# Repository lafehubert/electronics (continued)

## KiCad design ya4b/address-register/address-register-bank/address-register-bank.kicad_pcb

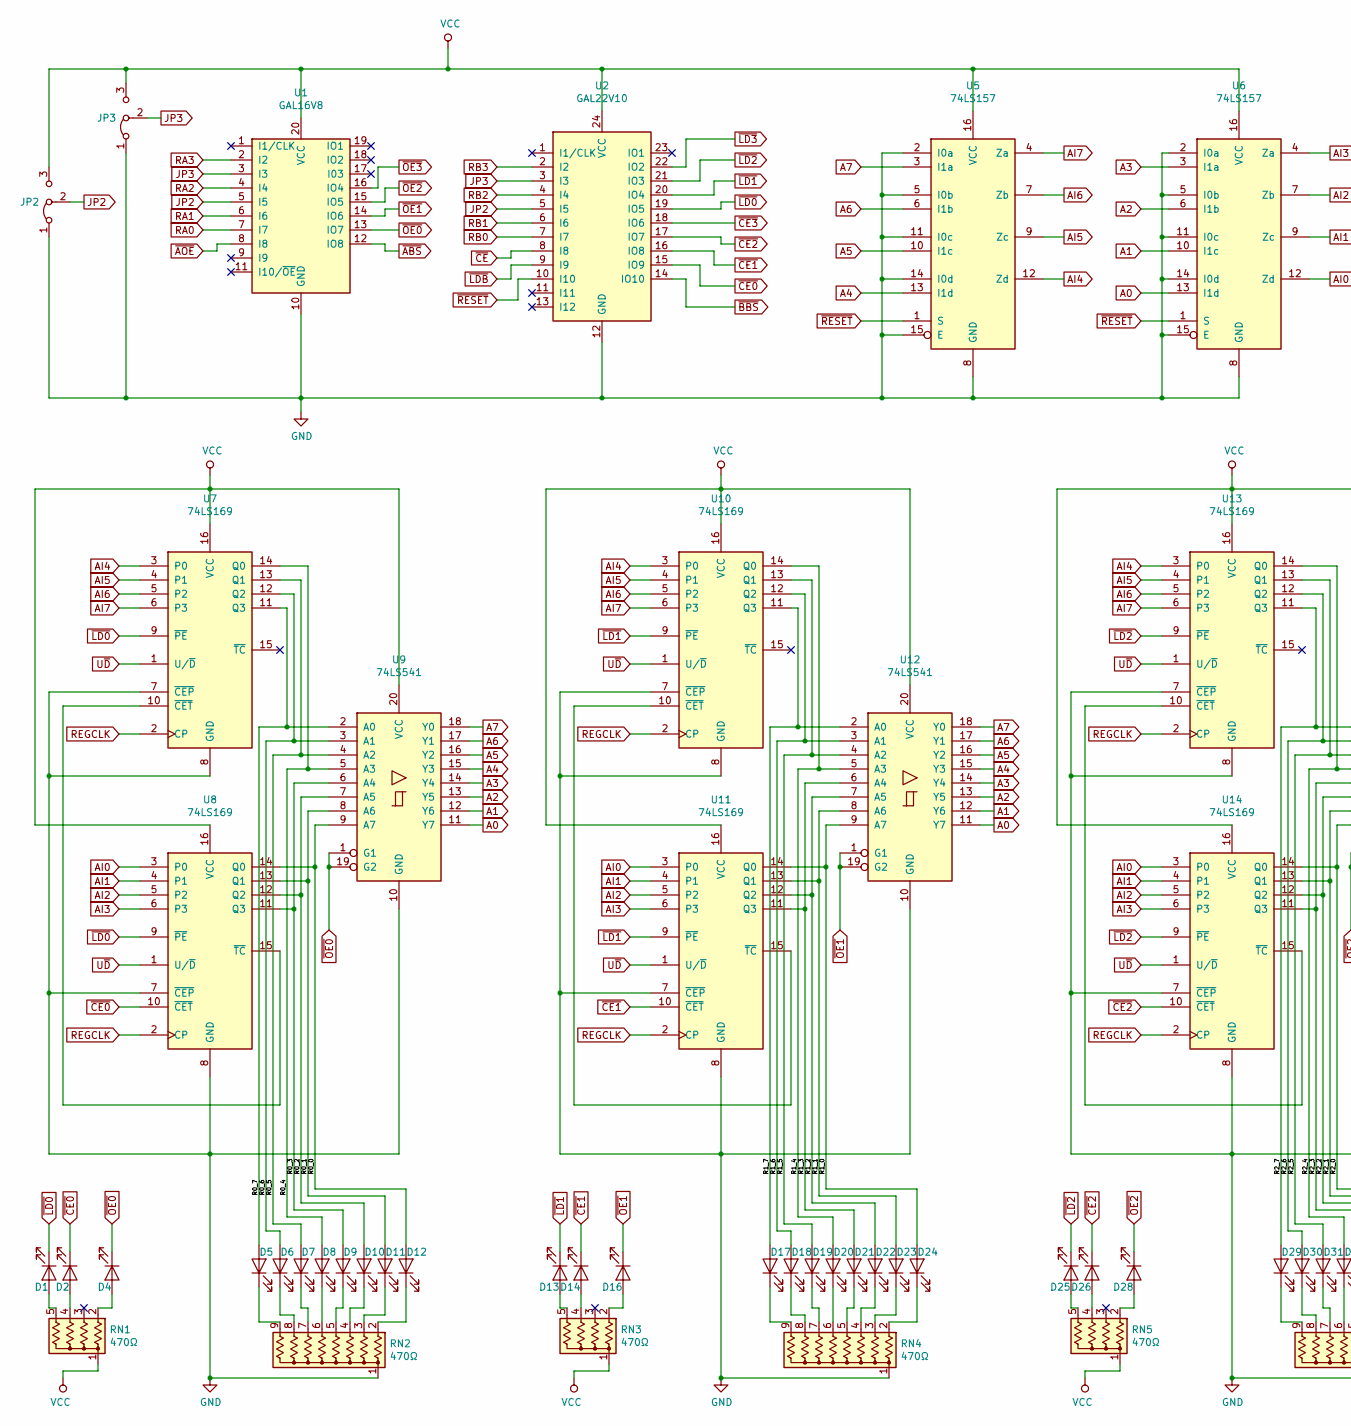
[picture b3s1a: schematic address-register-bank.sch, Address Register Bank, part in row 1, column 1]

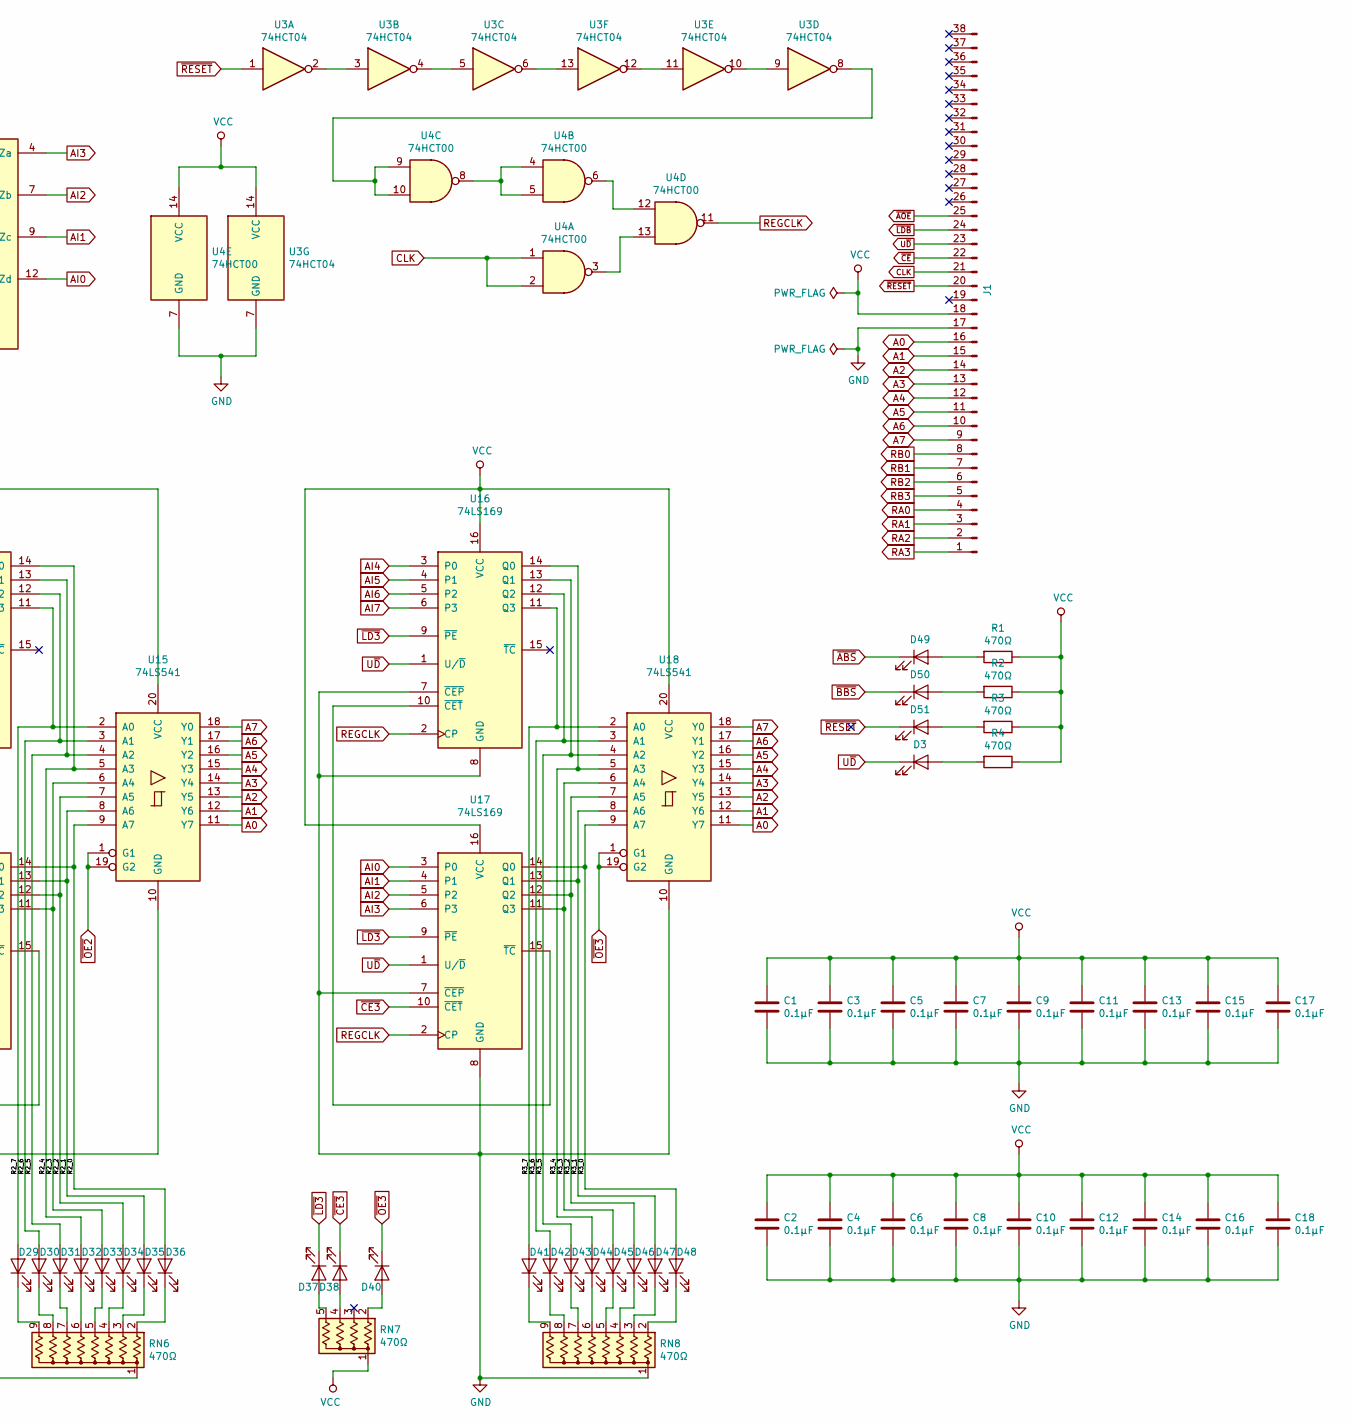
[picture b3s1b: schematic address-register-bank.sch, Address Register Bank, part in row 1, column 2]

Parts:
C1, C2, C3, C4, C5, C6, C7, C8, C9, C10, C11, C12, C13, C14, C15, C16, C17, C18: 0.1µF; C_Disc_D3.0mm_W1.6mm_P2.50mm
D1, D2, D3, D4, D5, D6, D7, D8, D9, D10, D11, D12, D13, D14, D16, D17, D18, D19, D20, D21, D22, D23, D24, D25, D26, D28, D29, D30, D31, D32, D33, D34, D35, D36, D37, D38, D40, D41, D42, D43, D44, D45, D46, D47, D48, D49, D50, D51: LED; LED_Rectangular_W5.0mm_H2.0mm
J1: Conn_01x38_Male; PinHeader_1x38_P2.54mm_Vertical
JP2, JP3: Jumper_3_Bridged12; PinHeader_1x03_P2.54mm_Vertical
R1, R2, R3, R4: 470Ω; R_Axial_DIN0207_L6.3mm_D2.5mm_P10.16mm_Horizontal
RN1, RN3, RN5, RN7: 470Ω; R_Array_SIP5
RN2, RN4, RN6, RN8: 470Ω; R_Array_SIP9
U1: GAL16V8; DIP-20_W7.62mm_Socket
U2: GAL22V10; DIP-24_W7.62mm_Socket
U3: 74HCT04; DIP-14_W7.62mm_Socket
U4: 74HCT00; DIP-14_W7.62mm_Socket
U5, U6: 74LS157; DIP-16_W7.62mm_Socket
U7, U8, U10, U11, U13, U14, U16, U17: 74LS169; DIP-16_W7.62mm_Socket
U9, U12, U15, U18: 74LS541; DIP-20_W7.62mm_Socket

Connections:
/R0_0: D12.2 (A), U8.14 (Q0), U9.9 (A7)
/R0_1: D11.2 (A), U8.13 (Q1), U9.8 (A6)
/R0_2: D10.2 (A), U8.12 (Q2), U9.7 (A5)
/R0_3: D9.2 (A), U8.11 (Q3), U9.6 (A4)
/R0_4: D8.2 (A), U7.14 (Q0), U9.5 (A3)
/R0_5: D7.2 (A), U7.13 (Q1), U9.4 (A2)
/R0_6: D6.2 (A), U7.12 (Q2), U9.3 (A1)
/R0_7: D5.2 (A), U7.11 (Q3), U9.2 (A0)
/R1_0: D24.2 (A), U11.14 (Q0), U12.9 (A7)
/R1_1: D23.2 (A), U11.13 (Q1), U12.8 (A6)
/R1_2: D22.2 (A), U11.12 (Q2), U12.7 (A5)
/R1_3: D21.2 (A), U11.11 (Q3), U12.6 (A4)
/R1_4: D20.2 (A), U10.14 (Q0), U12.5 (A3)
/R1_5: D19.2 (A), U10.13 (Q1), U12.4 (A2)
/R1_6: D18.2 (A), U10.12 (Q2), U12.3 (A1)
/R1_7: D17.2 (A), U10.11 (Q3), U12.2 (A0)
/R2_0: D36.2 (A), U14.14 (Q0), U15.9 (A7)
/R2_1: D35.2 (A), U14.13 (Q1), U15.8 (A6)
/R2_2: D34.2 (A), U14.12 (Q2), U15.7 (A5)
/R2_3: D33.2 (A), U14.11 (Q3), U15.6 (A4)
/R2_4: D32.2 (A), U13.14 (Q0), U15.5 (A3)
/R2_5: D31.2 (A), U13.13 (Q1), U15.4 (A2)
/R2_6: D30.2 (A), U13.12 (Q2), U15.3 (A1)
/R2_7: D29.2 (A), U13.11 (Q3), U15.2 (A0)
/R3_0: D48.2 (A), U17.14 (Q0), U18.9 (A7)
/R3_1: D47.2 (A), U17.13 (Q1), U18.8 (A6)
/R3_2: D46.2 (A), U17.12 (Q2), U18.7 (A5)
/R3_3: D45.2 (A), U17.11 (Q3), U18.6 (A4)
/R3_4: D44.2 (A), U16.14 (Q0), U18.5 (A3)
/R3_5: D43.2 (A), U16.13 (Q1), U18.4 (A2)
/R3_6: D42.2 (A), U16.12 (Q2), U18.3 (A1)
/R3_7: D41.2 (A), U16.11 (Q3), U18.2 (A0)
A0: J1.16, U6.13 (I1d), U9.11 (Y7), U12.11 (Y7), U15.11 (Y7), U18.11 (Y7)
A1: J1.15, U6.10 (I1c), U9.12 (Y6), U12.12 (Y6), U15.12 (Y6), U18.12 (Y6)
A2: J1.14, U6.6 (I1b), U9.13 (Y5), U12.13 (Y5), U15.13 (Y5), U18.13 (Y5)
A3: J1.13, U6.3 (I1a), U9.14 (Y4), U12.14 (Y4), U15.14 (Y4), U18.14 (Y4)
A4: J1.12, U5.13 (I1d), U9.15 (Y3), U12.15 (Y3), U15.15 (Y3), U18.15 (Y3)
A5: J1.11, U5.10 (I1c), U9.16 (Y2), U12.16 (Y2), U15.16 (Y2), U18.16 (Y2)
A6: J1.10, U5.6 (I1b), U9.17 (Y1), U12.17 (Y1), U15.17 (Y1), U18.17 (Y1)
A7: J1.9, U5.3 (I1a), U9.18 (Y0), U12.18 (Y0), U15.18 (Y0), U18.18 (Y0)
AI0: U6.12 (Zd), U8.3 (P0), U11.3 (P0), U14.3 (P0), U17.3 (P0)
AI1: U6.9 (Zc), U8.4 (P1), U11.4 (P1), U14.4 (P1), U17.4 (P1)
AI2: U6.7 (Zb), U8.5 (P2), U11.5 (P2), U14.5 (P2), U17.5 (P2)
AI3: U6.4 (Za), U8.6 (P3), U11.6 (P3), U14.6 (P3), U17.6 (P3)
AI4: U5.12 (Zd), U7.3 (P0), U10.3 (P0), U13.3 (P0), U16.3 (P0)
AI5: U5.9 (Zc), U7.4 (P1), U10.4 (P1), U13.4 (P1), U16.4 (P1)
AI6: U5.7 (Zb), U7.5 (P2), U10.5 (P2), U13.5 (P2), U16.5 (P2)
AI7: U5.4 (Za), U7.6 (P3), U10.6 (P3), U13.6 (P3), U16.6 (P3)
CLK: J1.21, U4.1, U4.2
GND: C1.2, C2.2, C3.2, C4.2, C5.2, C6.2, C7.2, C8.2, C9.2, C10.2, C11.2, C12.2, C13.2, C14.2, C15.2, C16.2, C17.2, C18.2, J1.17, JP2.1 (A), JP3.1 (A), RN2.1 (common), RN4.1 (common), RN6.1 (common), RN8.1 (common), U1.10 (GND), U2.12 (GND), U3.7 (GND), U4.7 (GND), U5.2 (I0a), U5.5 (I0b), U5.8 (GND), U5.11 (I0c), U5.14 (I0d), U5.15 (E), U6.2 (I0a), U6.5 (I0b), U6.8 (GND), U6.11 (I0c), U6.14 (I0d), U6.15 (E), U7.7 (~CEP), U7.8 (GND), U8.7 (~CEP), U8.8 (GND), U9.10 (GND), U10.7 (~CEP), U10.8 (GND), U11.7 (~CEP), U11.8 (GND), U12.10 (GND), U13.7 (~CEP), U13.8 (GND), U14.7 (~CEP), U14.8 (GND), U15.10 (GND), U16.7 (~CEP), U16.8 (GND), U17.7 (~CEP), U17.8 (GND), U18.10 (GND)
JP2: JP2.2 (C), U1.5 (I5), U2.5 (I5)
JP3: JP3.2 (C), U1.3 (I3), U2.3 (I3)
unnamed: D1.2 (A), RN1.5 (R4)
unnamed: D2.2 (A), RN1.4 (R3)
unnamed: D3.2 (A), R4.2
unnamed: D4.2 (A), RN1.2 (R1)
unnamed: D5.1 (K), RN2.9 (R8)
unnamed: D6.1 (K), RN2.8 (R7)
unnamed: D7.1 (K), RN2.7 (R6)
unnamed: D8.1 (K), RN2.6 (R5)
unnamed: D9.1 (K), RN2.5 (R4)
unnamed: D10.1 (K), RN2.4 (R3)
unnamed: D11.1 (K), RN2.3 (R2)
unnamed: D12.1 (K), RN2.2 (R1)
unnamed: D13.2 (A), RN3.5 (R4)
unnamed: D14.2 (A), RN3.4 (R3)
unnamed: D16.2 (A), RN3.2 (R1)
unnamed: D17.1 (K), RN4.9 (R8)
unnamed: D18.1 (K), RN4.8 (R7)
unnamed: D19.1 (K), RN4.7 (R6)
unnamed: D20.1 (K), RN4.6 (R5)
unnamed: D21.1 (K), RN4.5 (R4)
unnamed: D22.1 (K), RN4.4 (R3)
unnamed: D23.1 (K), RN4.3 (R2)
unnamed: D24.1 (K), RN4.2 (R1)
unnamed: D25.2 (A), RN5.5 (R4)
unnamed: D26.2 (A), RN5.4 (R3)
unnamed: D28.2 (A), RN5.2 (R1)
unnamed: D29.1 (K), RN6.9 (R8)
unnamed: D30.1 (K), RN6.8 (R7)
unnamed: D31.1 (K), RN6.7 (R6)
unnamed: D32.1 (K), RN6.6 (R5)
unnamed: D33.1 (K), RN6.5 (R4)
unnamed: D34.1 (K), RN6.4 (R3)
unnamed: D35.1 (K), RN6.3 (R2)
unnamed: D36.1 (K), RN6.2 (R1)
unnamed: D37.2 (A), RN7.5 (R4)
unnamed: D38.2 (A), RN7.4 (R3)
unnamed: D40.2 (A), RN7.2 (R1)
unnamed: D41.1 (K), RN8.9 (R8)
unnamed: D42.1 (K), RN8.8 (R7)
unnamed: D43.1 (K), RN8.7 (R6)
unnamed: D44.1 (K), RN8.6 (R5)
unnamed: D45.1 (K), RN8.5 (R4)
unnamed: D46.1 (K), RN8.4 (R3)
unnamed: D47.1 (K), RN8.3 (R2)
unnamed: D48.1 (K), RN8.2 (R1)
unnamed: D49.2 (A), R1.2
unnamed: D50.2 (A), R2.2
unnamed: D51.2 (A), R3.2
unnamed: U3.2, U3.3
unnamed: U3.4, U3.5
unnamed: U3.8, U4.9, U4.10
unnamed: U3.9, U3.10
unnamed: U3.11, U3.12
unnamed: U3.6, U3.13
unnamed: U4.4, U4.5, U4.8
unnamed: U4.6, U4.12
unnamed: U4.3, U4.13
unnamed: U7.10 (~CET), U8.15 (~TC)
unnamed: U10.10 (~CET), U11.15 (~TC)
unnamed: U13.10 (~CET), U14.15 (~TC)
unnamed: U16.10 (~CET), U17.15 (~TC)
RA0: J1.4, U1.7 (I7)
RA1: J1.3, U1.6 (I6)
RA2: J1.2, U1.4 (I4)
RA3: J1.1, U1.2 (I2)
RB0: J1.8, U2.7 (I7)
RB1: J1.7, U2.6 (I6)
RB2: J1.6, U2.4 (I4)
RB3: J1.5, U2.2 (I2)
REGCLK: U4.11, U7.2 (CP), U8.2 (CP), U10.2 (CP), U11.2 (CP), U13.2 (CP), U14.2 (CP), U16.2 (CP), U17.2 (CP)
U~D~: D3.1 (K), J1.23, U7.1 (U/~D), U8.1 (U/~D), U10.1 (U/~D), U11.1 (U/~D), U13.1 (U/~D), U14.1 (U/~D), U16.1 (U/~D), U17.1 (U/~D)
VCC: C1.1, C2.1, C3.1, C4.1, C5.1, C6.1, C7.1, C8.1, C9.1, C10.1, C11.1, C12.1, C13.1, C14.1, C15.1, C16.1, C17.1, C18.1, J1.18, JP2.3 (B), JP3.3 (B), R1.1, R2.1, R3.1, R4.1, RN1.1 (common), RN3.1 (common), RN5.1 (common), RN7.1 (common), U1.20 (VCC), U2.24 (VCC), U3.14 (VCC), U4.14 (VCC), U5.16 (VCC), U6.16 (VCC), U7.16 (VCC), U8.16 (VCC), U9.20 (VCC), U10.16 (VCC), U11.16 (VCC), U12.20 (VCC), U13.16 (VCC), U14.16 (VCC), U15.20 (VCC), U16.16 (VCC), U17.16 (VCC), U18.20 (VCC)
~ABS~: D49.1 (K), U1.12 (IO8)
~AOE~: J1.25, U1.8 (I8)
~BBS~: D50.1 (K), U2.14 (IO10)
~CE0~: D2.1 (K), U2.15 (IO9), U8.10 (~CET)
~CE1~: D14.1 (K), U2.16 (IO8), U11.10 (~CET)
~CE2~: D26.1 (K), U2.17 (IO7), U14.10 (~CET)
~CE3~: D38.1 (K), U2.18 (IO6), U17.10 (~CET)
~CE~: J1.22, U2.8 (I8)
~LD0~: D1.1 (K), U2.19 (IO5), U7.9 (~PE), U8.9 (~PE)
~LD1~: D13.1 (K), U2.20 (IO4), U10.9 (~PE), U11.9 (~PE)
~LD2~: D25.1 (K), U2.21 (IO3), U13.9 (~PE), U14.9 (~PE)
~LD3~: D37.1 (K), U2.22 (IO2), U16.9 (~PE), U17.9 (~PE)
~LDB~: J1.24, U2.9 (I9)
~OE0~: D4.1 (K), U1.13 (IO7), U9.1 (G1), U9.19 (G2)
~OE1~: D16.1 (K), U1.14 (IO6), U12.1 (G1), U12.19 (G2)
~OE2~: D28.1 (K), U1.15 (IO5), U15.1 (G1), U15.19 (G2)
~OE3~: D40.1 (K), U1.16 (IO4), U18.1 (G1), U18.19 (G2)
~RESET~: D51.1 (K), J1.20, U2.10 (I10), U3.1, U5.1 (S), U6.1 (S)

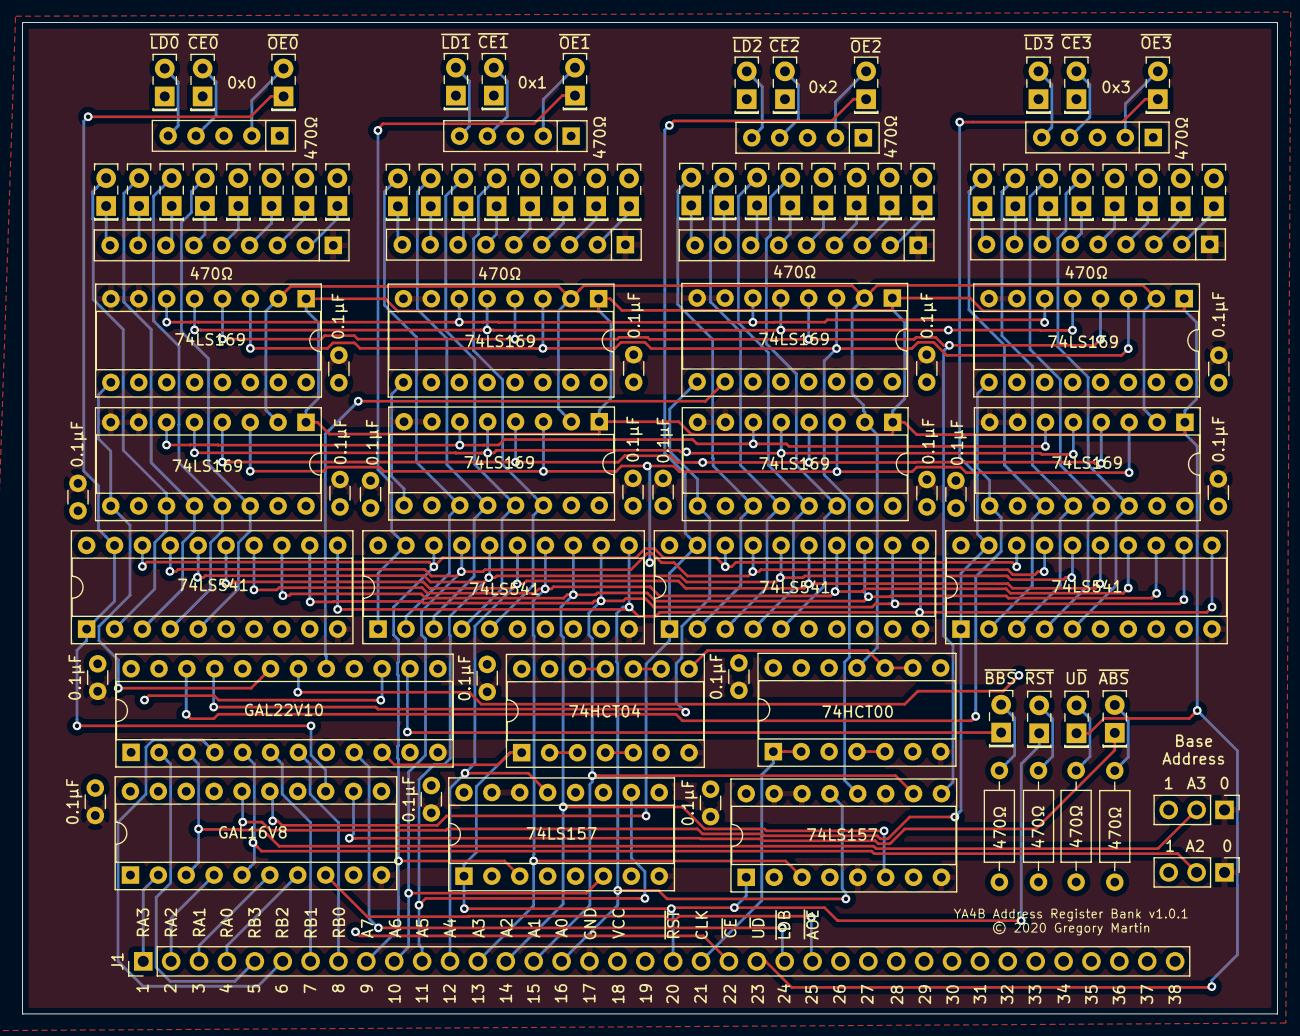
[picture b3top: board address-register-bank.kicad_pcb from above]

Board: 4 copper layers, 114.3 x 90.3 mm, 99 parts (0 on the bottom side), 142 nets.

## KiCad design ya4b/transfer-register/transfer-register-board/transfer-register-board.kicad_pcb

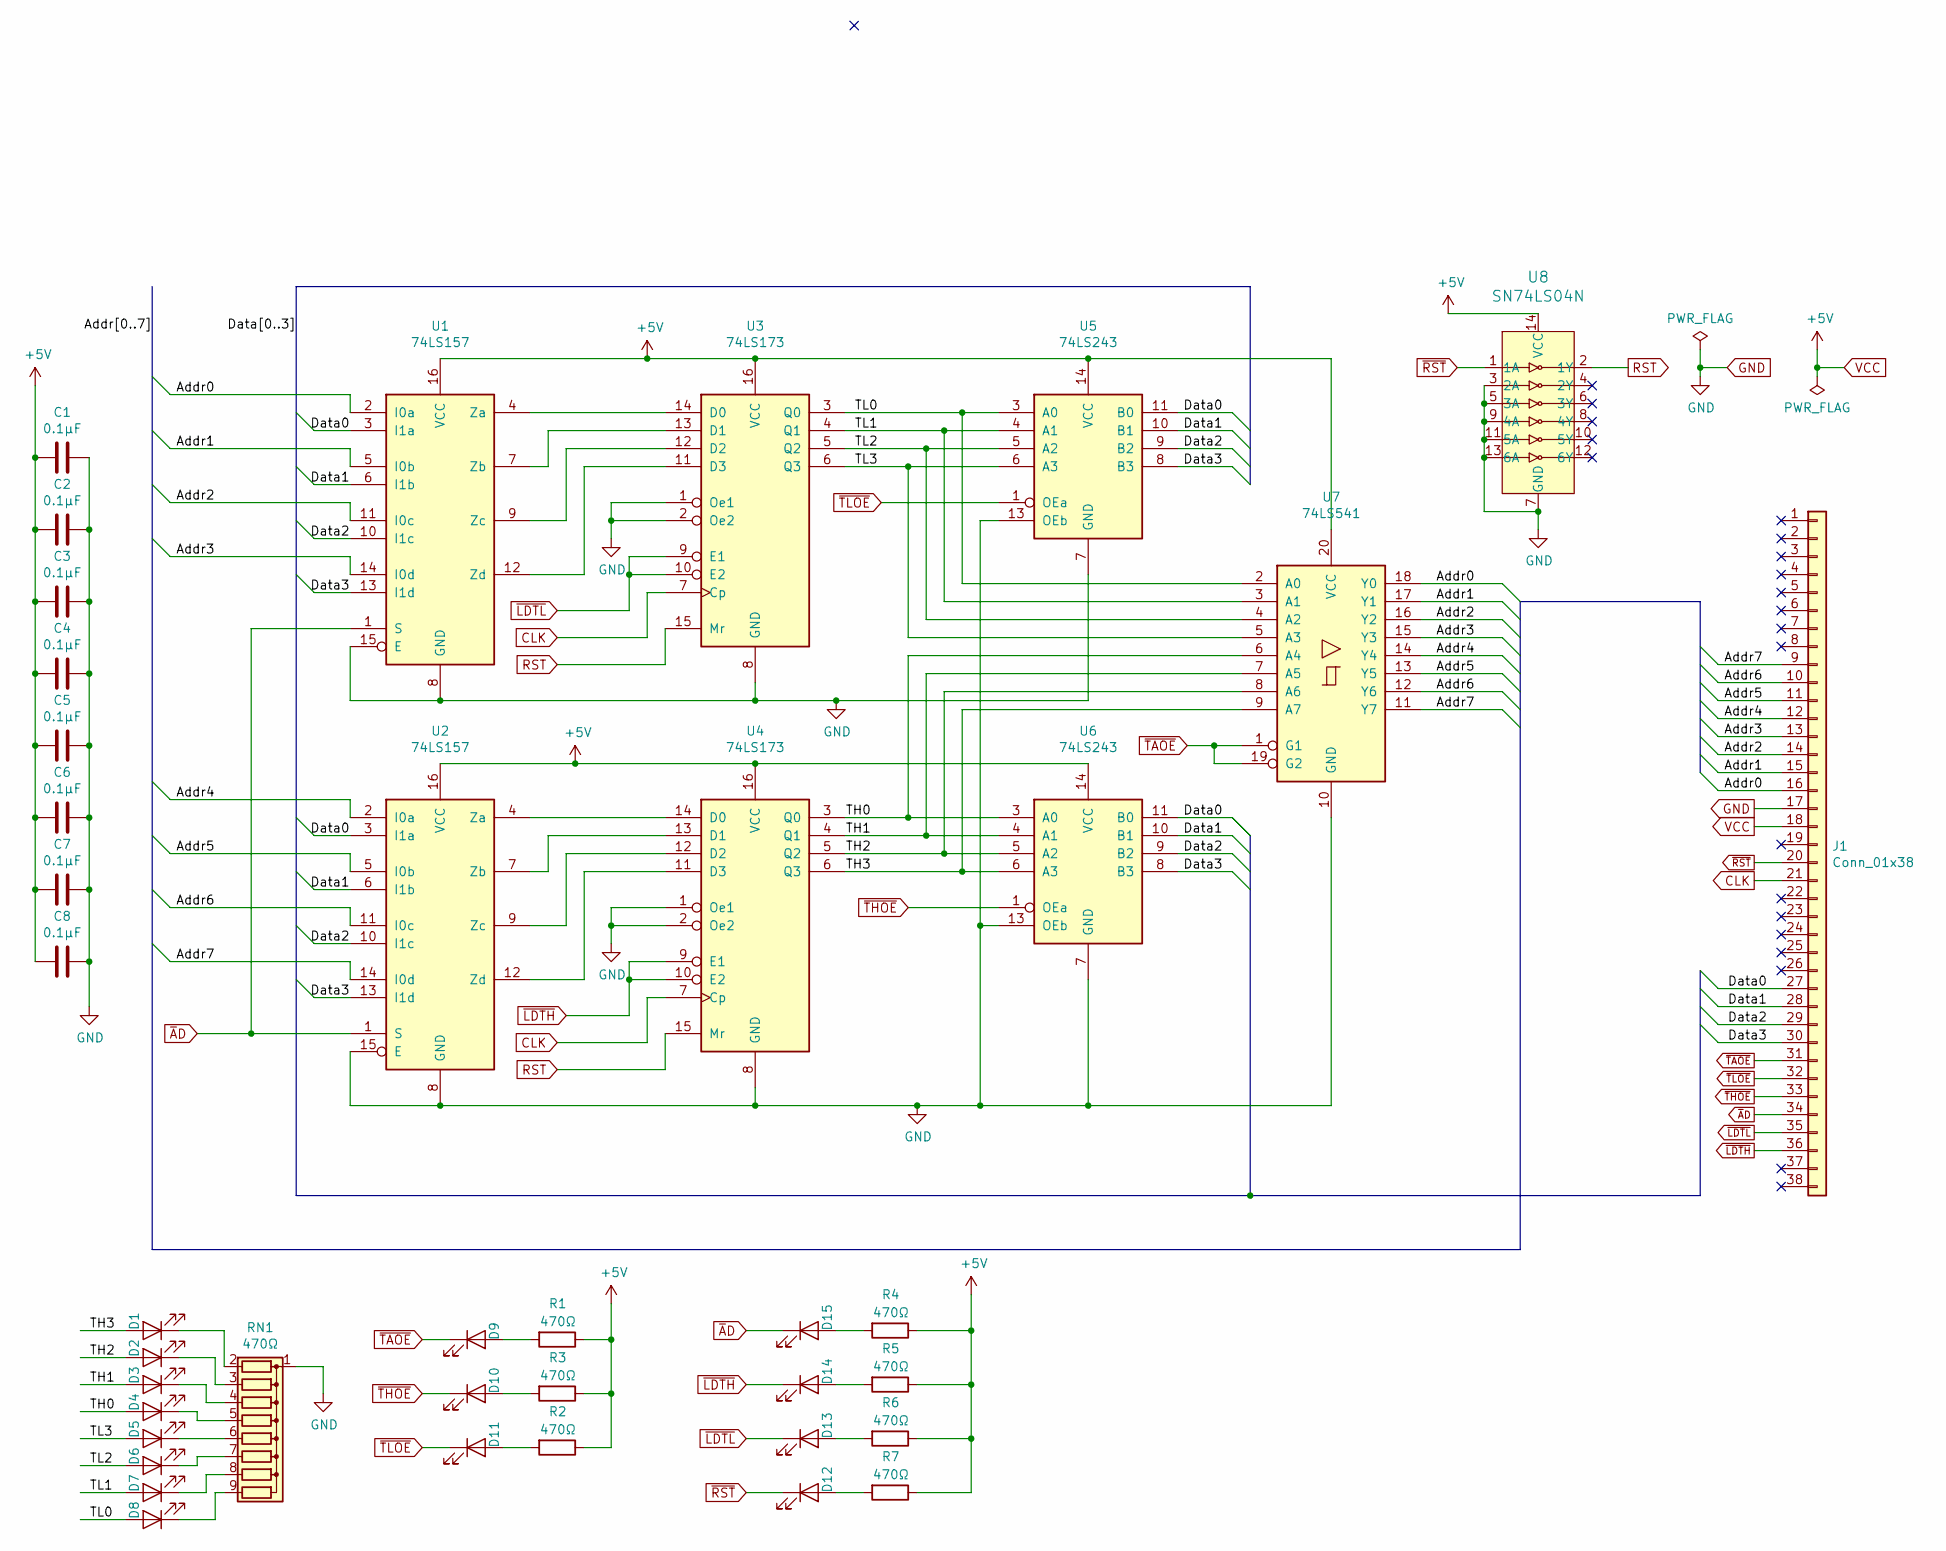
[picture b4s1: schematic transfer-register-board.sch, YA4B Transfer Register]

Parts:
C1, C2, C3, C4, C5, C6, C7, C8: 0.1µF; C_Disc_D3.4mm_W2.1mm_P2.50mm
D1, D2, D3, D4, D5, D6, D7, D8, D9, D10, D11, D12, D13, D14, D15: LED; LED_Rectangular_W5.0mm_H2.0mm
J1: Conn_01x38; PinHeader_1x38_P2.54mm_Vertical
R1, R2, R3, R4, R5, R6, R7: 470Ω; R_Axial_DIN0207_L6.3mm_D2.5mm_P10.16mm_Horizontal
RN1: 470Ω; R_Array_SIP9
U1, U2: 74LS157; DIP-16_W7.62mm_Socket
U3, U4: 74LS173; DIP-16_W7.62mm_Socket
U5, U6: 74LS243; DIP-14_W7.62mm_Socket
U7: 74LS541; DIP-20_W7.62mm_Socket
U8: SN74LS04N; DIP-14_W7.62mm_Socket; MPN SN74LS04N; Digi-Key_PN 296-1629-5-ND

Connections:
/Addr0: J1.16, U1.2 (I0a), U7.18 (Y0)
/Addr1: J1.15, U1.5 (I0b), U7.17 (Y1)
/Addr2: J1.14, U1.11 (I0c), U7.16 (Y2)
/Addr3: J1.13, U1.14 (I0d), U7.15 (Y3)
/Addr4: J1.12, U2.2 (I0a), U7.14 (Y4)
/Addr5: J1.11, U2.5 (I0b), U7.13 (Y5)
/Addr6: J1.10, U2.11 (I0c), U7.12 (Y6)
/Addr7: J1.9, U2.14 (I0d), U7.11 (Y7)
/Data0: J1.27, U1.3 (I1a), U2.3 (I1a), U5.11 (B0), U6.11 (B0)
/Data1: J1.28, U1.6 (I1b), U2.6 (I1b), U5.10 (B1), U6.10 (B1)
/Data2: J1.29, U1.10 (I1c), U2.10 (I1c), U5.9 (B2), U6.9 (B2)
/Data3: J1.30, U1.13 (I1d), U2.13 (I1d), U5.8 (B3), U6.8 (B3)
/TH0: D4.2 (A), U4.3 (Q0), U6.3 (A0), U7.6 (A4)
/TH1: D3.2 (A), U4.4 (Q1), U6.4 (A1), U7.7 (A5)
/TH2: D2.2 (A), U4.5 (Q2), U6.5 (A2), U7.8 (A6)
/TH3: D1.2 (A), U4.6 (Q3), U6.6 (A3), U7.9 (A7)
/TL0: D8.2 (A), U3.3 (Q0), U5.3 (A0), U7.2 (A0)
/TL1: D7.2 (A), U3.4 (Q1), U5.4 (A1), U7.3 (A1)
/TL2: D6.2 (A), U3.5 (Q2), U5.5 (A2), U7.4 (A2)
/TL3: D5.2 (A), U3.6 (Q3), U5.6 (A3), U7.5 (A3)
CLK: J1.21, U3.7 (Cp), U4.7 (Cp)
GND: C1.1, C2.1, C3.1, C4.1, C5.1, C6.1, C7.1, C8.1, J1.17, RN1.1 (common), U1.8 (GND), U1.15 (E), U2.8 (GND), U2.15 (E), U3.1 (Oe1), U3.2 (Oe2), U3.8 (GND), U4.1 (Oe1), U4.2 (Oe2), U4.8 (GND), U5.7 (GND), U5.13 (OEb), U6.7 (GND), U6.13 (OEb), U7.10 (GND), U8.3 (2A), U8.5 (3A), U8.7 (GND), U8.9 (4A), U8.11 (5A), U8.13 (6A)
unnamed: D1.1 (K), RN1.2 (R1)
unnamed: D2.1 (K), RN1.3 (R2)
unnamed: D3.1 (K), RN1.4 (R3)
unnamed: D4.1 (K), RN1.5 (R4)
unnamed: D5.1 (K), RN1.6 (R5)
unnamed: D6.1 (K), RN1.7 (R6)
unnamed: D7.1 (K), RN1.8 (R7)
unnamed: D8.1 (K), RN1.9 (R8)
unnamed: D9.2 (A), R1.2
unnamed: D10.2 (A), R3.2
unnamed: D11.2 (A), R2.2
unnamed: D12.2 (A), R7.2
unnamed: D13.2 (A), R6.2
unnamed: D14.2 (A), R5.2
unnamed: D15.2 (A), R4.2
unnamed: U1.4 (Za), U3.14 (D0)
unnamed: U1.7 (Zb), U3.13 (D1)
unnamed: U1.9 (Zc), U3.12 (D2)
unnamed: U1.12 (Zd), U3.11 (D3)
unnamed: U2.4 (Za), U4.14 (D0)
unnamed: U2.7 (Zb), U4.13 (D1)
unnamed: U2.9 (Zc), U4.12 (D2)
unnamed: U2.12 (Zd), U4.11 (D3)
RST: U3.15 (Mr), U4.15 (Mr), U8.2 (1Y)
VCC: C1.2, C2.2, C3.2, C4.2, C5.2, C6.2, C7.2, C8.2, J1.18, R1.1, R2.1, R3.1, R4.1, R5.1, R6.1, R7.1, U1.16 (VCC), U2.16 (VCC), U3.16 (VCC), U4.16 (VCC), U5.14 (VCC), U6.14 (VCC), U7.20 (VCC), U8.14 (VCC)
~A~D: D15.1 (K), J1.34, U1.1 (S), U2.1 (S)
~LDTH~: D14.1 (K), J1.36, U4.9 (E1), U4.10 (E2)
~LDTL~: D13.1 (K), J1.35, U3.9 (E1), U3.10 (E2)
~RST~: D12.1 (K), J1.20, U8.1 (1A)
~TAOE~: D9.1 (K), J1.31, U7.1 (G1), U7.19 (G2)
~THOE~: D10.1 (K), J1.33, U6.1 (OEa)
~TLOE~: D11.1 (K), J1.32, U5.1 (OEa)

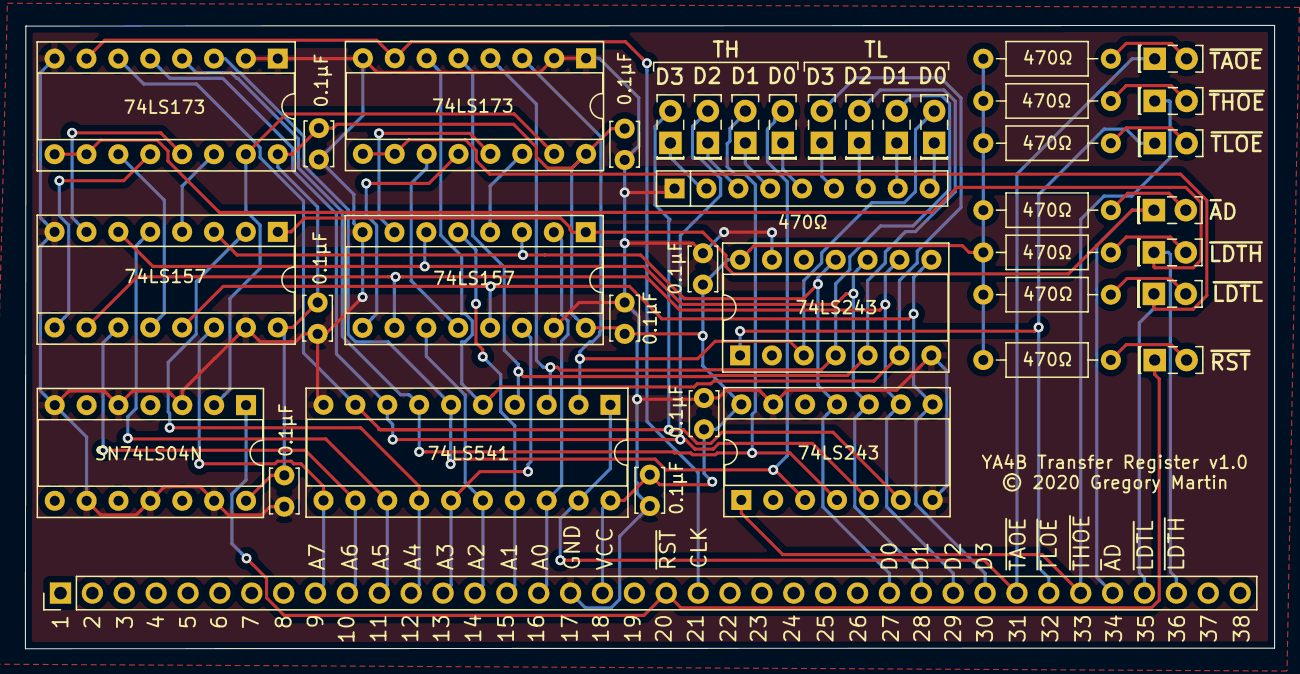
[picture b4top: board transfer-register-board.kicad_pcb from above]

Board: 2 copper layers, 99.5 x 49.7 mm, 40 parts (0 on the bottom side), 54 nets.

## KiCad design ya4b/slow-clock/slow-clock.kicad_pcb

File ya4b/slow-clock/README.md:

This slow clock was initially inspired by Ben Eater's design (https://eater.net/8bit/clock) but I found the 555 to be too fiddly for the monostable stage, and overkill for the bistable stage, so I used a 74LS123 for the former and an R-S latch made from a couple of NANDs on a 74LS00 for the latter.  I also replaced the 74LS04 with a 74LS14 which seemed to clean up the waveform a good bit.

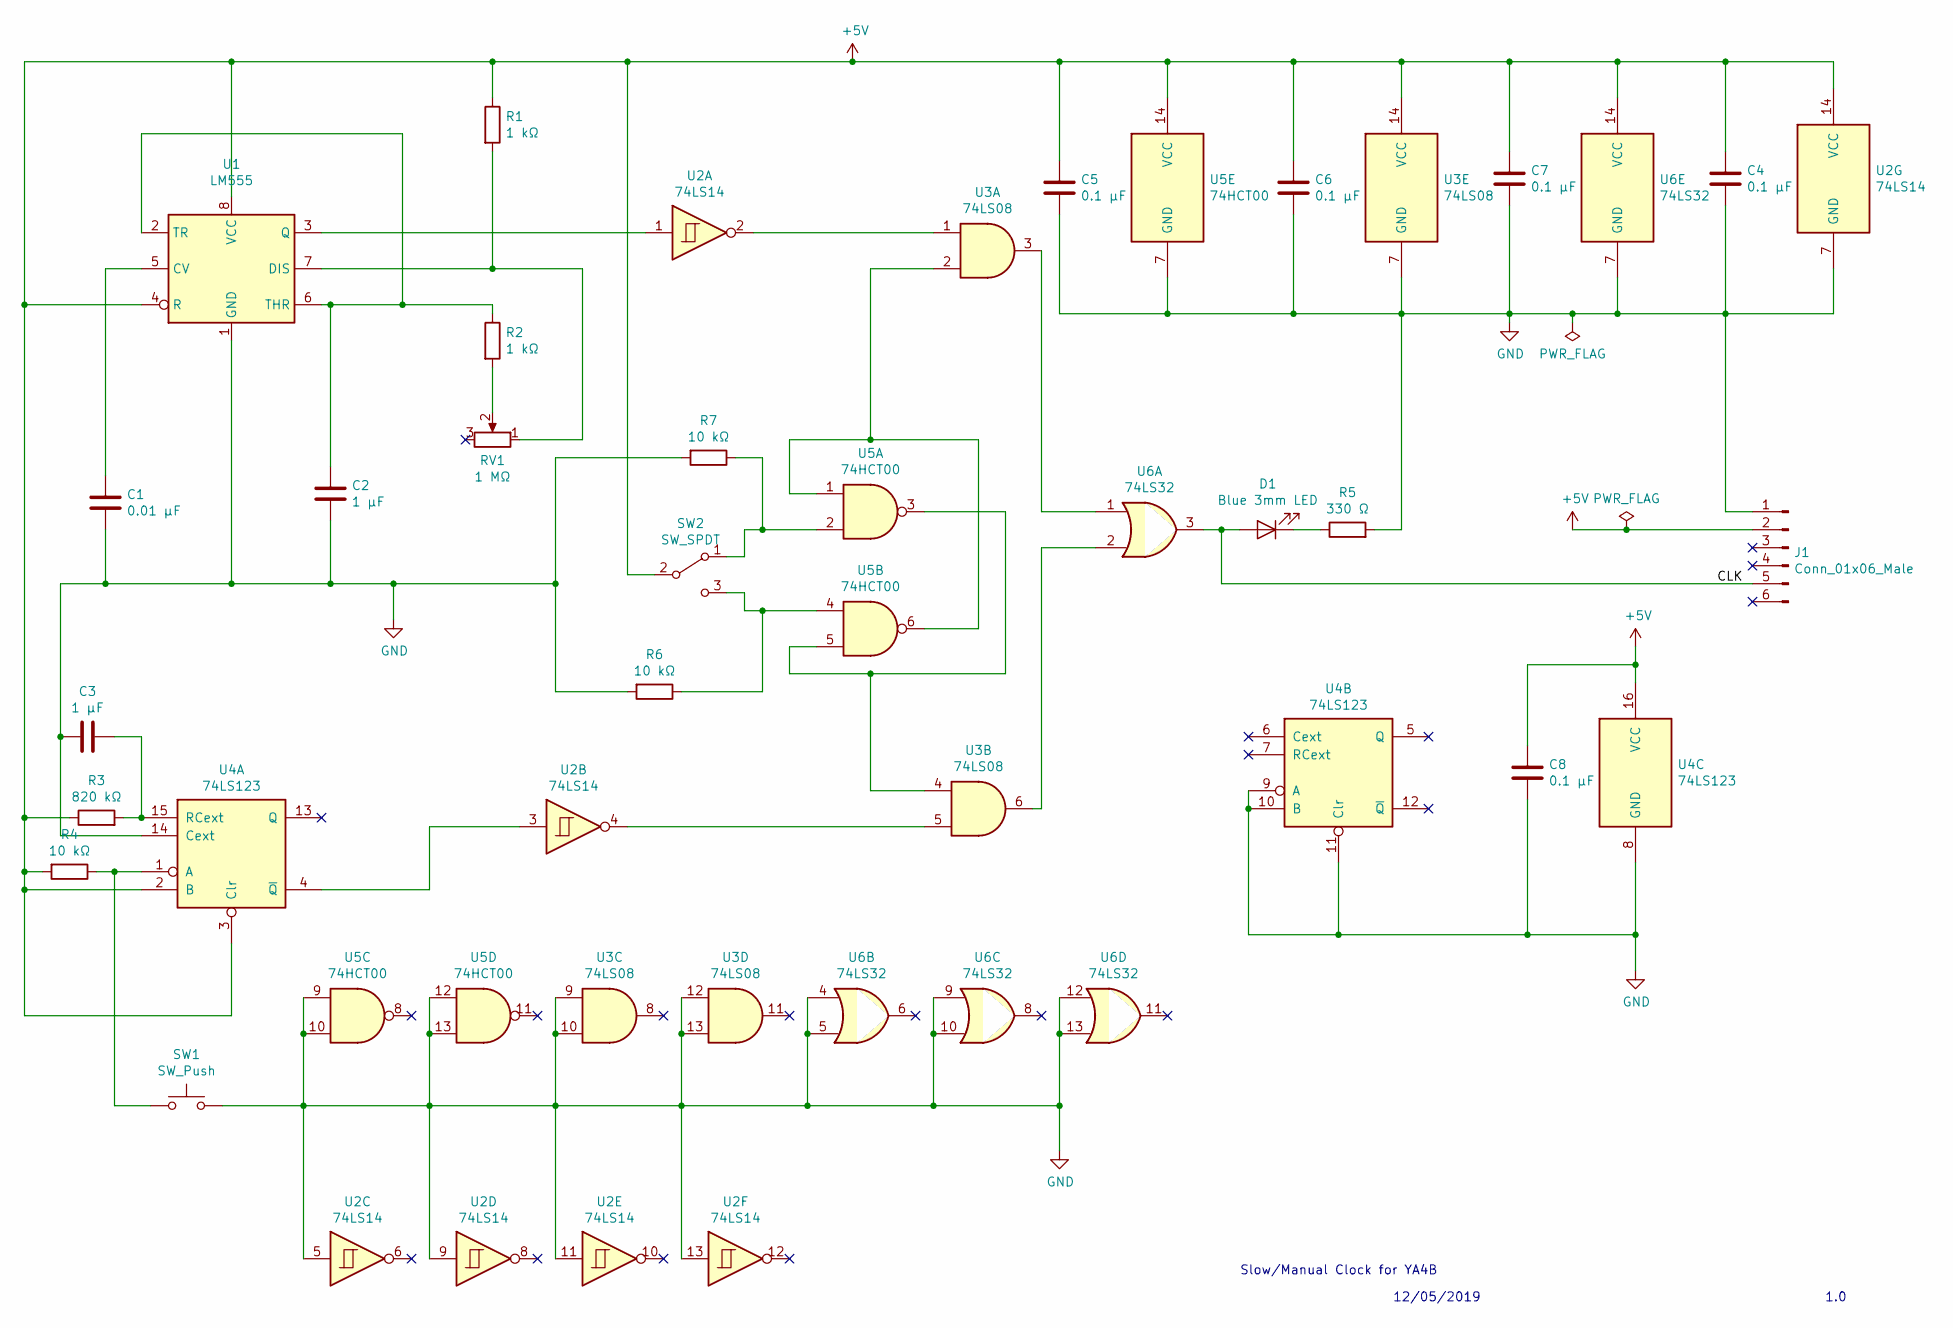
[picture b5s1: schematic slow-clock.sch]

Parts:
C1: 0.01 µF; C_Disc_D3.8mm_W2.6mm_P2.50mm
C2, C3: 1 µF; C_Disc_D3.8mm_W2.6mm_P2.50mm
C4, C5, C6, C7, C8: 0.1 µF; C_Disc_D3.8mm_W2.6mm_P2.50mm
D1: Blue 3mm LED; LED_D3.0mm
J1: Conn_01x06_Male; PinHeader_1x06_P2.54mm_Vertical
R1, R2: 1 kΩ; R_Axial_DIN0207_L6.3mm_D2.5mm_P10.16mm_Horizontal
R3: 820 kΩ; R_Axial_DIN0207_L6.3mm_D2.5mm_P10.16mm_Horizontal
R4, R6, R7: 10 kΩ; R_Axial_DIN0207_L6.3mm_D2.5mm_P10.16mm_Horizontal
R5: 330 Ω; R_Axial_DIN0207_L6.3mm_D2.5mm_P10.16mm_Horizontal
RV1: 1 MΩ; GM_Small_Square_9mm_Pot
SW1: SW_Push; SW_PUSH_6mm
SW2: SW_SPDT; GM_SPDT_Slide_Switch
U1: LM555; DIP-8_W7.62mm_Socket
U2: 74LS14; DIP-14_W7.62mm_Socket
U3: 74LS08; DIP-14_W7.62mm_Socket
U4: 74LS123; DIP-16_W7.62mm_Socket
U5: 74HCT00; DIP-14_W7.62mm_Socket
U6: 74LS32; DIP-14_W7.62mm_Socket

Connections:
+5V: C4.1, C5.1, C6.1, C7.1, C8.1, J1.2, R1.1, R3.1, R4.2, SW2.2 (B), U1.4 (R), U1.8 (VCC), U2.14 (VCC), U3.14 (VCC), U4.2 (B), U4.3 (Clr), U4.16 (VCC), U5.14 (VCC), U6.14 (VCC)
/CLK: D1.2 (A), J1.5, U6.3
GND: C1.2, C2.2, C3.2, C4.2, C5.2, C6.2, C7.2, C8.2, J1.1, R5.2, R6.2, R7.2, SW1.2, U1.1 (GND), U2.5, U2.7 (GND), U2.9, U2.11, U2.13, U3.7 (GND), U3.9, U3.10, U3.12, U3.13, U4.8 (GND), U4.9 (A), U4.10 (B), U4.11 (Clr), U4.14 (Cext), U5.7 (GND), U5.9, U5.10, U5.12, U5.13, U6.4, U6.5, U6.7 (GND), U6.9, U6.10, U6.12, U6.13
unnamed: C1.1, U1.5 (CV)
unnamed: C2.1, R2.1, U1.2 (TR), U1.6 (THR)
unnamed: C3.1, R3.2, U4.15 (RCext)
unnamed: D1.1 (K), R5.1
unnamed: R1.2, RV1.1, U1.7 (DIS)
unnamed: R2.2, RV1.2
unnamed: R4.1, SW1.1, U4.1 (A)
unnamed: R6.1, SW2.3 (C), U5.4
unnamed: R7.1, SW2.1 (A), U5.2
unnamed: U1.3 (Q), U2.1
unnamed: U2.2, U3.1
unnamed: U2.3, U4.4 (~Q)
unnamed: U2.4, U3.5
unnamed: U3.2, U5.1, U5.6
unnamed: U3.3, U6.1
unnamed: U3.4, U5.3, U5.5
unnamed: U3.6, U6.2

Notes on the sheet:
Slow/Manual Clock for YA4B
12/05/2019
1.0

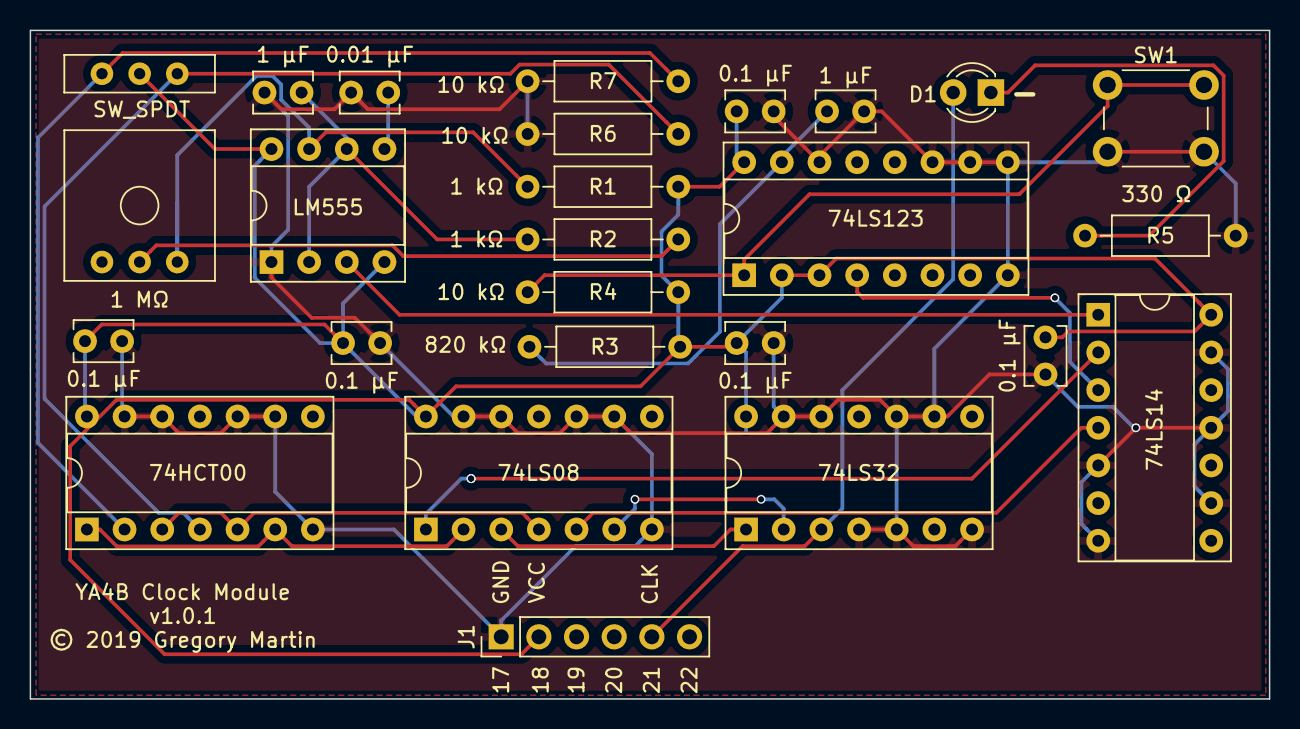
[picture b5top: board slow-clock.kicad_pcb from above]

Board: 2 copper layers, 83.6 x 45.1 mm, 26 parts (0 on the bottom side), 20 nets.
